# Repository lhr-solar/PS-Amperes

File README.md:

# BPS-AmperesPCB - Firmware

- To do: update readme

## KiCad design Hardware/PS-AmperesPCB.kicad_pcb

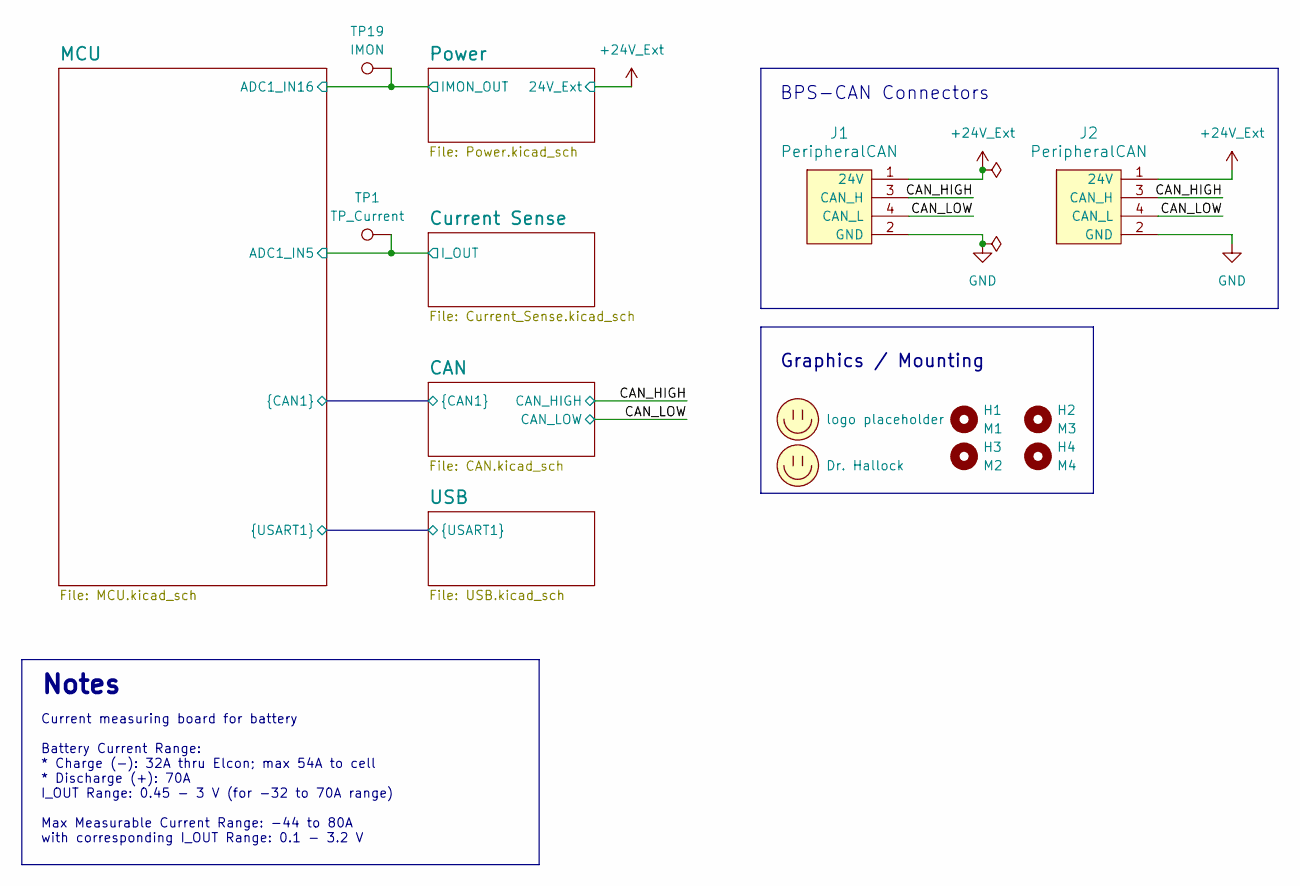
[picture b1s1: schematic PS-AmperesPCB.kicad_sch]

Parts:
H1: M1; MountingHole_3.2mm_M3_DIN965_Pad_TopBottom
H2: M3; MountingHole_3.2mm_M3_DIN965_Pad_TopBottom
H3: M2; MountingHole_3.2mm_M3_DIN965_Pad_TopBottom
H4: M4; MountingHole_3.2mm_M3_DIN965_Pad_TopBottom
J1, J2: PeripheralCAN; Molex_Nano-Fit_105309-xx04_1x04_P2.50mm_Vertical
LOGO1: logo placeholder; LHRs_LOGO
LOGO2: Dr. Hallock; Hallock_Image_Tiny
TP1: TP_Current; TestPoint_Keystone_5005-5009_Compact
TP19: IMON; TestPoint_Keystone_5005-5009_Compact

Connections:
+24V_Ext: J1.1 (24V), J2.1 (24V); also elsewhere on the board
/CAN_HIGH: J1.3 (CAN_H), J2.3 (CAN_H); also elsewhere on the board
/CAN_LOW: J1.4 (CAN_L), J2.4 (CAN_L); also elsewhere on the board
/Current Sense/I_OUT: TP1.1; also elsewhere on the board
/MCU/ADC1_IN16: TP19.1; also elsewhere on the board
GND: J1.2 (GND), J2.2 (GND); also elsewhere on the board

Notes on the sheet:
Notes
Graphics / Mounting
Current measuring board for battery Battery Current Range: * Charge (-): 32A thru Elcon; max 54A to cell * Discharge (+): 70A I_OUT Range: 0.45 - 3 V (for -32 to 70A range) Max Measurable Current Range: -44 to 80A with corresponding I_OUT Range: 0.1 - 3.2 V
BPS-CAN Connectors

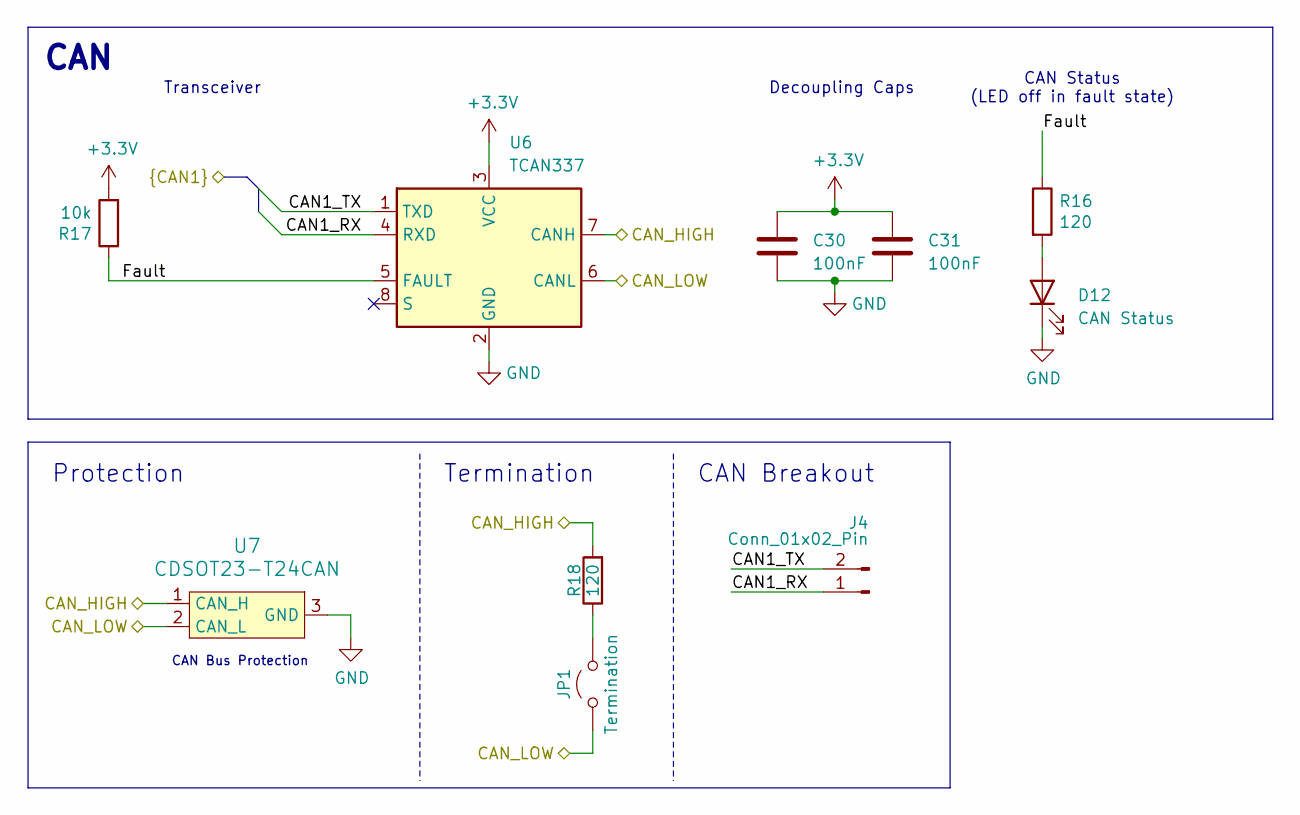
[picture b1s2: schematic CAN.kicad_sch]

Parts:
C30, C31: 100nF; C_0603_1608Metric_Pad1.08x0.95mm_HandSolder; Mouser Part Number 80-C0805C104M5R
D12: CAN Status; LED_0603_1608Metric_Pad1.05x0.95mm_HandSolder
J4: Conn_01x02_Pin; PinHeader_1x02_P2.54mm_Vertical
JP1: Termination; PinHeader_1x02_P2.54mm_Vertical
R16: 120; R_0603_1608Metric_Pad0.98x0.95mm_HandSolder; Mouser Part Number Inventory
R17: 10k; R_0603_1608Metric_Pad0.98x0.95mm_HandSolder
R18: 120; R_0603_1608Metric_Pad0.98x0.95mm_HandSolder; Mouser Part Number 71-CRCW080559R0FKEA
U6: TCAN337; TCAN337DCNR
U7: CDSOT23-T24CAN

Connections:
+3.3V: C30.1, C31.1, R17.2, U6.3 (VCC); also elsewhere on the board
/CAN/CAN1_RX: J4.1, U6.4 (RXD); also elsewhere on the board
/CAN/CAN1_TX: J4.2, U6.1 (TXD); also elsewhere on the board
/CAN/Fault: R16.1, R17.1, U6.5 (FAULT)
/CAN_HIGH: R18.2, U6.7 (CANH), U7.1 (CAN_H); also elsewhere on the board
/CAN_LOW: JP1.1 (A), U6.6 (CANL), U7.2 (CAN_L); also elsewhere on the board
GND: C30.2, C31.2, D12.1 (K), U6.2 (GND), U7.3 (GND); also elsewhere on the board
unnamed: D12.2 (A), R16.2
unnamed: JP1.2 (B), R18.1

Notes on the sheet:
Transceiver
CAN Breakout
Decoupling Caps
Protection
CAN Status (LED off in fault state)
Termination
CAN
CAN Bus Protection

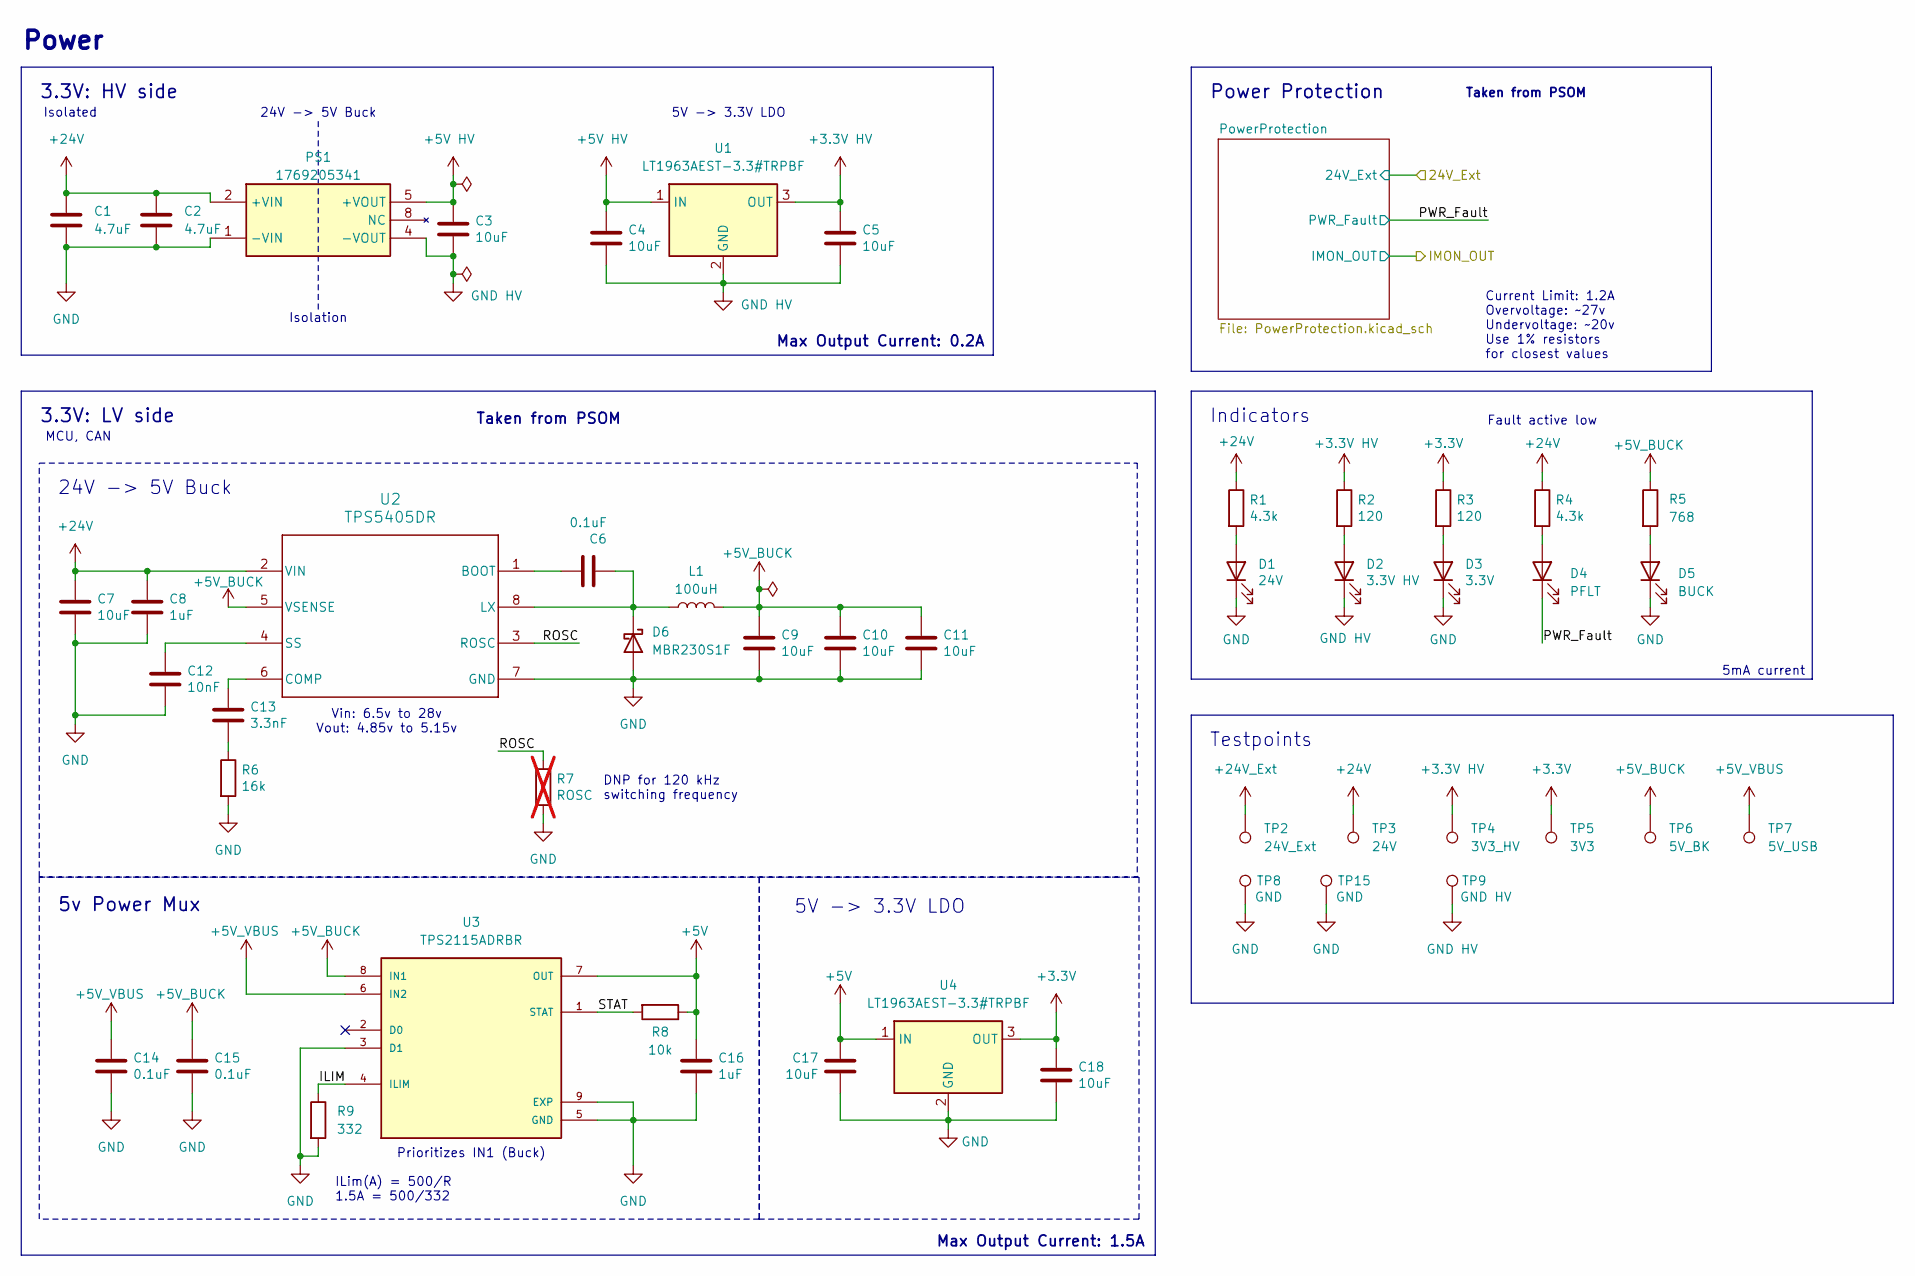
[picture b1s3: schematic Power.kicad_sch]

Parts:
C1, C2: 4.7uF; C_0805_2012Metric_Pad1.18x1.45mm_HandSolder
C3, C4, C5, C7, C9, C10, C11, C17, C18: 10uF; C_0805_2012Metric_Pad1.18x1.45mm_HandSolder
C6, C14, C15: 0.1uF; C_0603_1608Metric_Pad1.08x0.95mm_HandSolder
C8, C16: 1uF; C_0603_1608Metric_Pad1.08x0.95mm_HandSolder
C12: 10nF; C_0603_1608Metric_Pad1.08x0.95mm_HandSolder
C13: 3.3nF; C_0603_1608Metric_Pad1.08x0.95mm_HandSolder
D1: 24V; LED_0603_1608Metric_Pad1.05x0.95mm_HandSolder
D2: 3.3V HV; LED_0603_1608Metric_Pad1.05x0.95mm_HandSolder
D3: 3.3V; LED_0603_1608Metric_Pad1.05x0.95mm_HandSolder
D4: PFLT; LED_0603_1608Metric_Pad1.05x0.95mm_HandSolder
D5: BUCK; LED_0603_1608Metric_Pad1.05x0.95mm_HandSolder
D6: MBR230S1F; D_SOD-123F
L1: 100uH; L_Coilcraft_MSS1246-XXX
PS1: 1769205341; WE_1769205341; Mouser Part Number 710-1769205341
R1, R4: 4.3k; R_0603_1608Metric_Pad0.98x0.95mm_HandSolder
R2, R3: 120; R_0603_1608Metric_Pad0.98x0.95mm_HandSolder
R5: 768; R_0603_1608Metric_Pad0.98x0.95mm_HandSolder
R6: 16k; R_0603_1608Metric_Pad0.98x0.95mm_HandSolder
R7: ROSC; R_0603_1608Metric_Pad0.98x0.95mm_HandSolder; not fitted
R8: 10k; R_0603_1608Metric_Pad0.98x0.95mm_HandSolder
R9: 332; R_0603_1608Metric_Pad0.98x0.95mm_HandSolder
TP2: 24V_Ext; TestPoint_Pad_1.0x1.0mm
TP3: 24V; TestPoint_Pad_1.0x1.0mm
TP4: 3V3_HV; TestPoint_Pad_1.0x1.0mm
TP5: 3V3; TestPoint_Pad_1.0x1.0mm
TP6: 5V_BK; TestPoint_Pad_1.0x1.0mm
TP7: 5V_USB; TestPoint_Pad_1.0x1.0mm
TP8, TP15: GND; TestPoint_Pad_1.0x1.0mm
TP9: GND HV; TestPoint_Pad_1.0x1.0mm
U1, U4: LT1963AEST-3.3#TRPBF; SOT-223-3_TabPin2
U2: TPS5405DR
U3: TPS2115ADRBR; VSON-8-1EP_3x3mm_P0.65mm_EP1.65x2.4mm

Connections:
+3.3V: C18.1, R3.1, TP5.1, U4.3 (OUT); also elsewhere on the board
+3.3V HV: C5.1, R2.1, TP4.1, U1.3 (OUT); also elsewhere on the board
+5V: C16.1, C17.1, R8.1, U3.7 (OUT), U4.1 (IN)
+5V HV: C3.1, C4.1, PS1.5 (+VOUT), U1.1 (IN)
+5V_BUCK: C9.1, C10.1, C11.1, C15.1, L1.2, R5.1, TP6.1, U2.5 (VSENSE), U3.8 (IN1)
+5V_VBUS: C14.1, TP7.1, U3.6 (IN2); also elsewhere on the board
+24V: C1.1, C2.1, C7.1, C8.1, PS1.2 (+VIN), R1.1, R4.1, TP3.1, U2.2 (VIN); also elsewhere on the board
+24V_Ext: TP2.1; also elsewhere on the board
/Power/ILIM: R9.1, U3.4 (ILIM)
/Power/PWR_Fault: D4.1 (K); also elsewhere on the board
/Power/ROSC: R7.1, U2.3 (ROSC)
/Power/STAT: R8.2, U3.1 (STAT)
GND: C1.2, C2.2, C7.2, C8.2, C9.2, C10.2, C11.2, C12.2, C14.2, C15.2, C16.2, C17.2, C18.2, D1.1 (K), D3.1 (K), D5.1 (K), D6.2 (A), PS1.1 (-VIN), R6.2, R7.2, R9.2, TP8.1, TP15.1, U2.7 (GND), U3.3 (D1), U3.5 (GND), U3.9 (EXP), U4.2 (GND); also elsewhere on the board
GND HV: C3.2, C4.2, C5.2, D2.1 (K), PS1.4 (-VOUT), TP9.1, U1.2 (GND); also elsewhere on the board
unnamed: C13.2, R6.1
unnamed: D1.2 (A), R1.2
unnamed: D2.2 (A), R2.2
unnamed: D3.2 (A), R3.2
unnamed: D4.2 (A), R4.2
unnamed: D5.2 (A), R5.2
unnamed: C6.2, D6.1 (K), L1.1, U2.8 (LX)
unnamed: C6.1, U2.1 (BOOT)
unnamed: C13.1, U2.6 (COMP)
unnamed: C12.1, U2.4 (SS)

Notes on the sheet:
Isolation
Max Output Current: 1.5A
Power
Testpoints
Isolated
Taken from PSOM
Indicators
Max Output Current: 0.2A
3.3V: HV side
Prioritizes IN1 (Buck)
5v Power Mux
24V -> 5V Buck
5V -> 3.3V LDO
Current Limit: 1.2A Overvoltage: ~27v Undervoltage: ~20v Use 1% resistors for closest values
DNP for 120 kHz switching frequency
ILim(A) = 500/R 1.5A = 500/332
Vin: 6.5v to 28v Vout: 4.85v to 5.15v
5mA current
MCU, CAN
3.3V: LV side
Power Protection
Fault active low

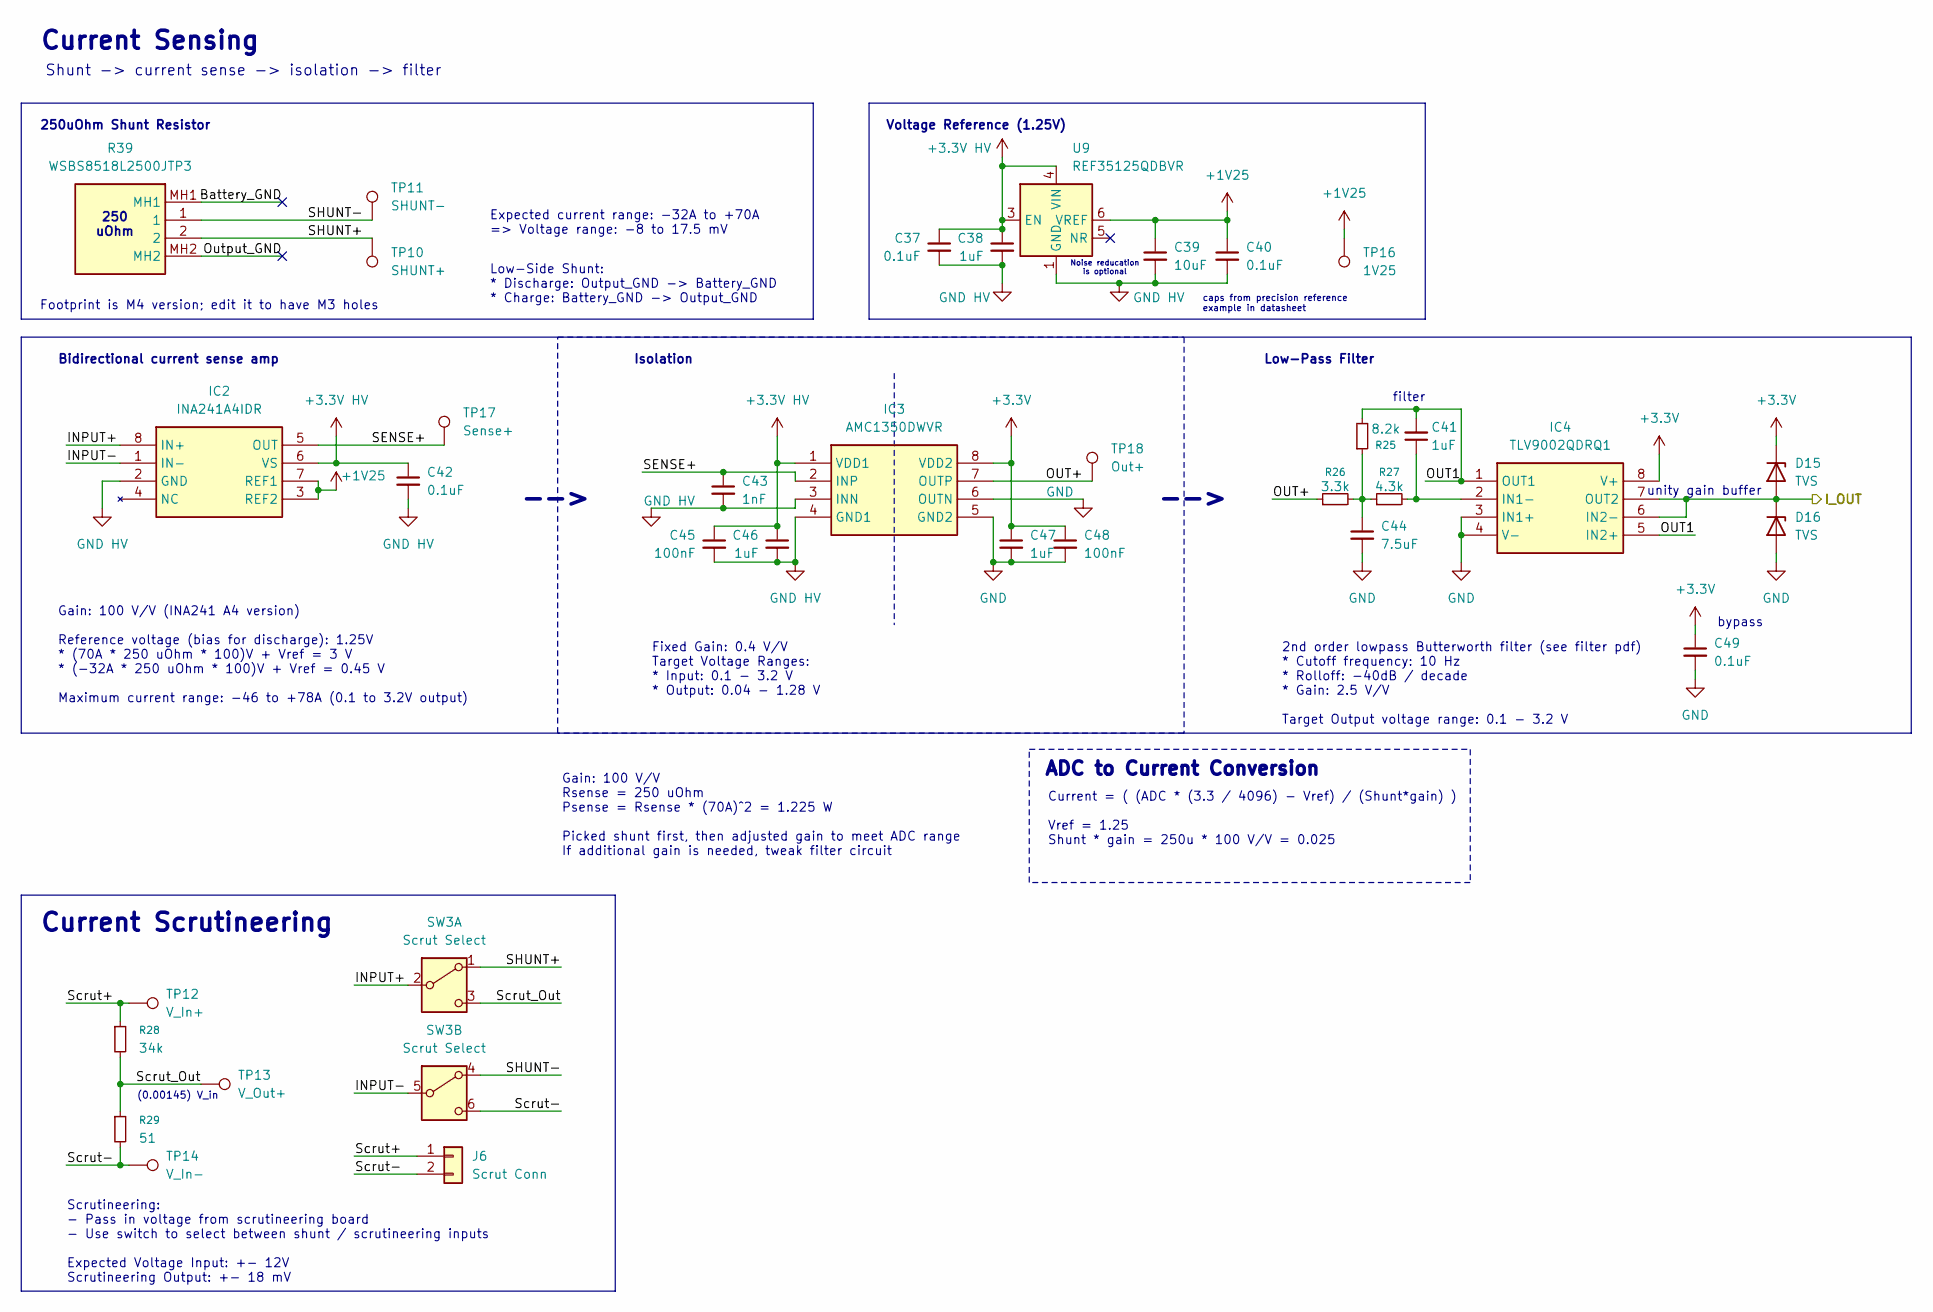
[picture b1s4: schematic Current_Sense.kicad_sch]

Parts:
C37, C40, C42, C49: 0.1uF; C_0603_1608Metric_Pad1.08x0.95mm_HandSolder
C38, C41, C46, C47: 1uF; C_0603_1608Metric_Pad1.08x0.95mm_HandSolder
C39: 10uF; C_0805_2012Metric_Pad1.18x1.45mm_HandSolder
C43: 1nF; C_0603_1608Metric_Pad1.08x0.95mm_HandSolder
C44: 7.5uF; C_0603_1608Metric_Pad1.08x0.95mm_HandSolder
C45, C48: 100nF; C_0603_1608Metric_Pad1.08x0.95mm_HandSolder
D15, D16: TVS; D_SOD-123F; Mouser Part Number 576-SMF3.3
IC2: INA241A4IDR; INA241A5IDR; Mouser Part Number 595-INA241A4IDR
IC3: AMC1350DWVR; Mouser Part Number 595-AMC1350DWVR
IC4: TLV9002QDRQ1; Mouser Part Number 595-TLV9002QDRQ1
J6: Scrut Conn; Molex_Nano-Fit_105309-xx02_1x02_P2.50mm_Vertical
R25: 8.2k; R_0603_1608Metric_Pad0.98x0.95mm_HandSolder
R26: 3.3k; R_0603_1608Metric_Pad0.98x0.95mm_HandSolder
R27: 4.3k; R_0603_1608Metric_Pad0.98x0.95mm_HandSolder
R28: 34k; R_0603_1608Metric_Pad0.98x0.95mm_HandSolder
R29: 51; R_0603_1608Metric_Pad0.98x0.95mm_HandSolder
R39: WSBS8518L2500JTP3; WSBS8518L2500JKM4; Mouser Part Number 71-WSBS8518L2500JTP3
SW3: Scrut Select; CAS220TB
TP10: SHUNT+; TestPoint_Pad_1.0x1.0mm
TP11: SHUNT-; TestPoint_Pad_1.0x1.0mm
TP12: V_In+; TestPoint_Pad_1.0x1.0mm
TP13: V_Out+; TestPoint_Pad_1.0x1.0mm
TP14: V_In-; TestPoint_Pad_1.0x1.0mm
TP16: 1V25; TestPoint_Pad_1.0x1.0mm
TP17: Sense+; TestPoint_Keystone_5005-5009_Compact
TP18: Out+; TestPoint_Keystone_5005-5009_Compact
U9: REF35125QDBVR; SOT-23-6

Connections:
+1V25: C39.1, C40.1, IC2.3 (REF2), IC2.7 (REF1), TP16.1, U9.6 (VREF)
+3.3V: C47.1, C48.1, C49.1, D15.1 (K), IC3.8 (VDD2), IC4.8 (V+); also elsewhere on the board
+3.3V HV: C37.1, C38.1, C42.1, C45.1, C46.1, IC2.6 (VS), IC3.1 (VDD1), U9.3 (EN), U9.4 (VIN); also elsewhere on the board
/Current Sense/Battery_GND: R39.MH1
/Current Sense/INPUT+: IC2.8 (IN+), SW3.2 (B)
/Current Sense/INPUT-: IC2.1 (IN-), SW3.5 (B)
/Current Sense/I_OUT: D15.2 (A), D16.1 (K), IC4.6 (IN2-), IC4.7 (OUT2); also elsewhere on the board
/Current Sense/OUT1: C41.2, IC4.1 (OUT1), IC4.5 (IN2+), R25.2
/Current Sense/OUT+: IC3.7 (OUTP), R26.1, TP18.1
/Current Sense/Output_GND: R39.MH2
/Current Sense/SENSE+: C43.1, IC2.5 (OUT), IC3.2 (INP), TP17.1
/Current Sense/SHUNT+: R39.2, SW3.1 (A), TP10.1
/Current Sense/SHUNT-: R39.1, SW3.4 (A), TP11.1
/Current Sense/Scrut+: J6.1, R28.1, TP12.1
/Current Sense/Scrut-: J6.2, R29.2, SW3.6 (C), TP14.1
/Current Sense/Scrut_Out: R28.2, R29.1, SW3.3 (C), TP13.1
GND: C44.2, C47.2, C48.2, C49.2, D16.2 (A), IC3.5 (GND2), IC3.6 (OUTN), IC4.3 (IN1+), IC4.4 (V-); also elsewhere on the board
GND HV: C37.2, C38.2, C39.2, C40.2, C42.2, C43.2, C45.2, C46.2, IC2.2 (GND), IC3.3 (INN), IC3.4 (GND1), U9.1 (GND), U9.2 (GND); also elsewhere on the board
unnamed: C44.1, R25.1, R26.2, R27.1
unnamed: C41.1, IC4.2 (IN1-), R27.2

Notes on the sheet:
Gain: 100 V/V (INA241 A4 version) Reference voltage (bias for discharge): 1.25V * (70A * 250 uOhm * 100)V + Vref = 3 V * (-32A * 250 uOhm * 100)V + Vref = 0.45 V Maximum current range: -46 to +78A (0.1 to 3.2V output)
-->
(0.00145) V_in
filter
unity gain buffer
Current Sensing
Fixed Gain: 0.4 V/V Target Voltage Ranges: * Input: 0.1 - 3.2 V * Output: 0.04 - 1.28 V
Bidirectional current sense amp
Current = ( (ADC * (3.3 / 4096) - Vref) / (Shunt*gain) ) Vref = 1.25 Shunt * gain = 250u * 100 V/V = 0.025
Gain: 100 V/V Rsense = 250 uOhm Psense = Rsense * (70A)^2 = 1.225 W Picked shunt first, then adjusted gain to meet ADC range If additional gain is needed, tweak filter circuit
Low-Side Shunt: * Discharge: Output_GND -> Battery_GND * Charge: Battery_GND -> Output_GND
ADC to Current Conversion
Isolation
Low-Pass Filter
250 uOhm
Scrutineering: - Pass in voltage from scrutineering board - Use switch to select between shunt / scrutineering inputs Expected Voltage Input: +- 12V Scrutineering Output: +- 18 mV
Shunt -> current sense -> isolation -> filter
Current Scrutineering
Voltage Reference (1.25V)
250uOhm Shunt Resistor
bypass
caps from precision reference example in datasheet
Expected current range: -32A to +70A => Voltage range: -8 to 17.5 mV
2nd order lowpass Butterworth filter (see filter pdf) * Cutoff frequency: 10 Hz * Rolloff: -40dB / decade * Gain: 2.5 V/V Target Output voltage range: 0.1 - 3.2 V
Noise reducation is optional
Footprint is M4 version; edit it to have M3 holes

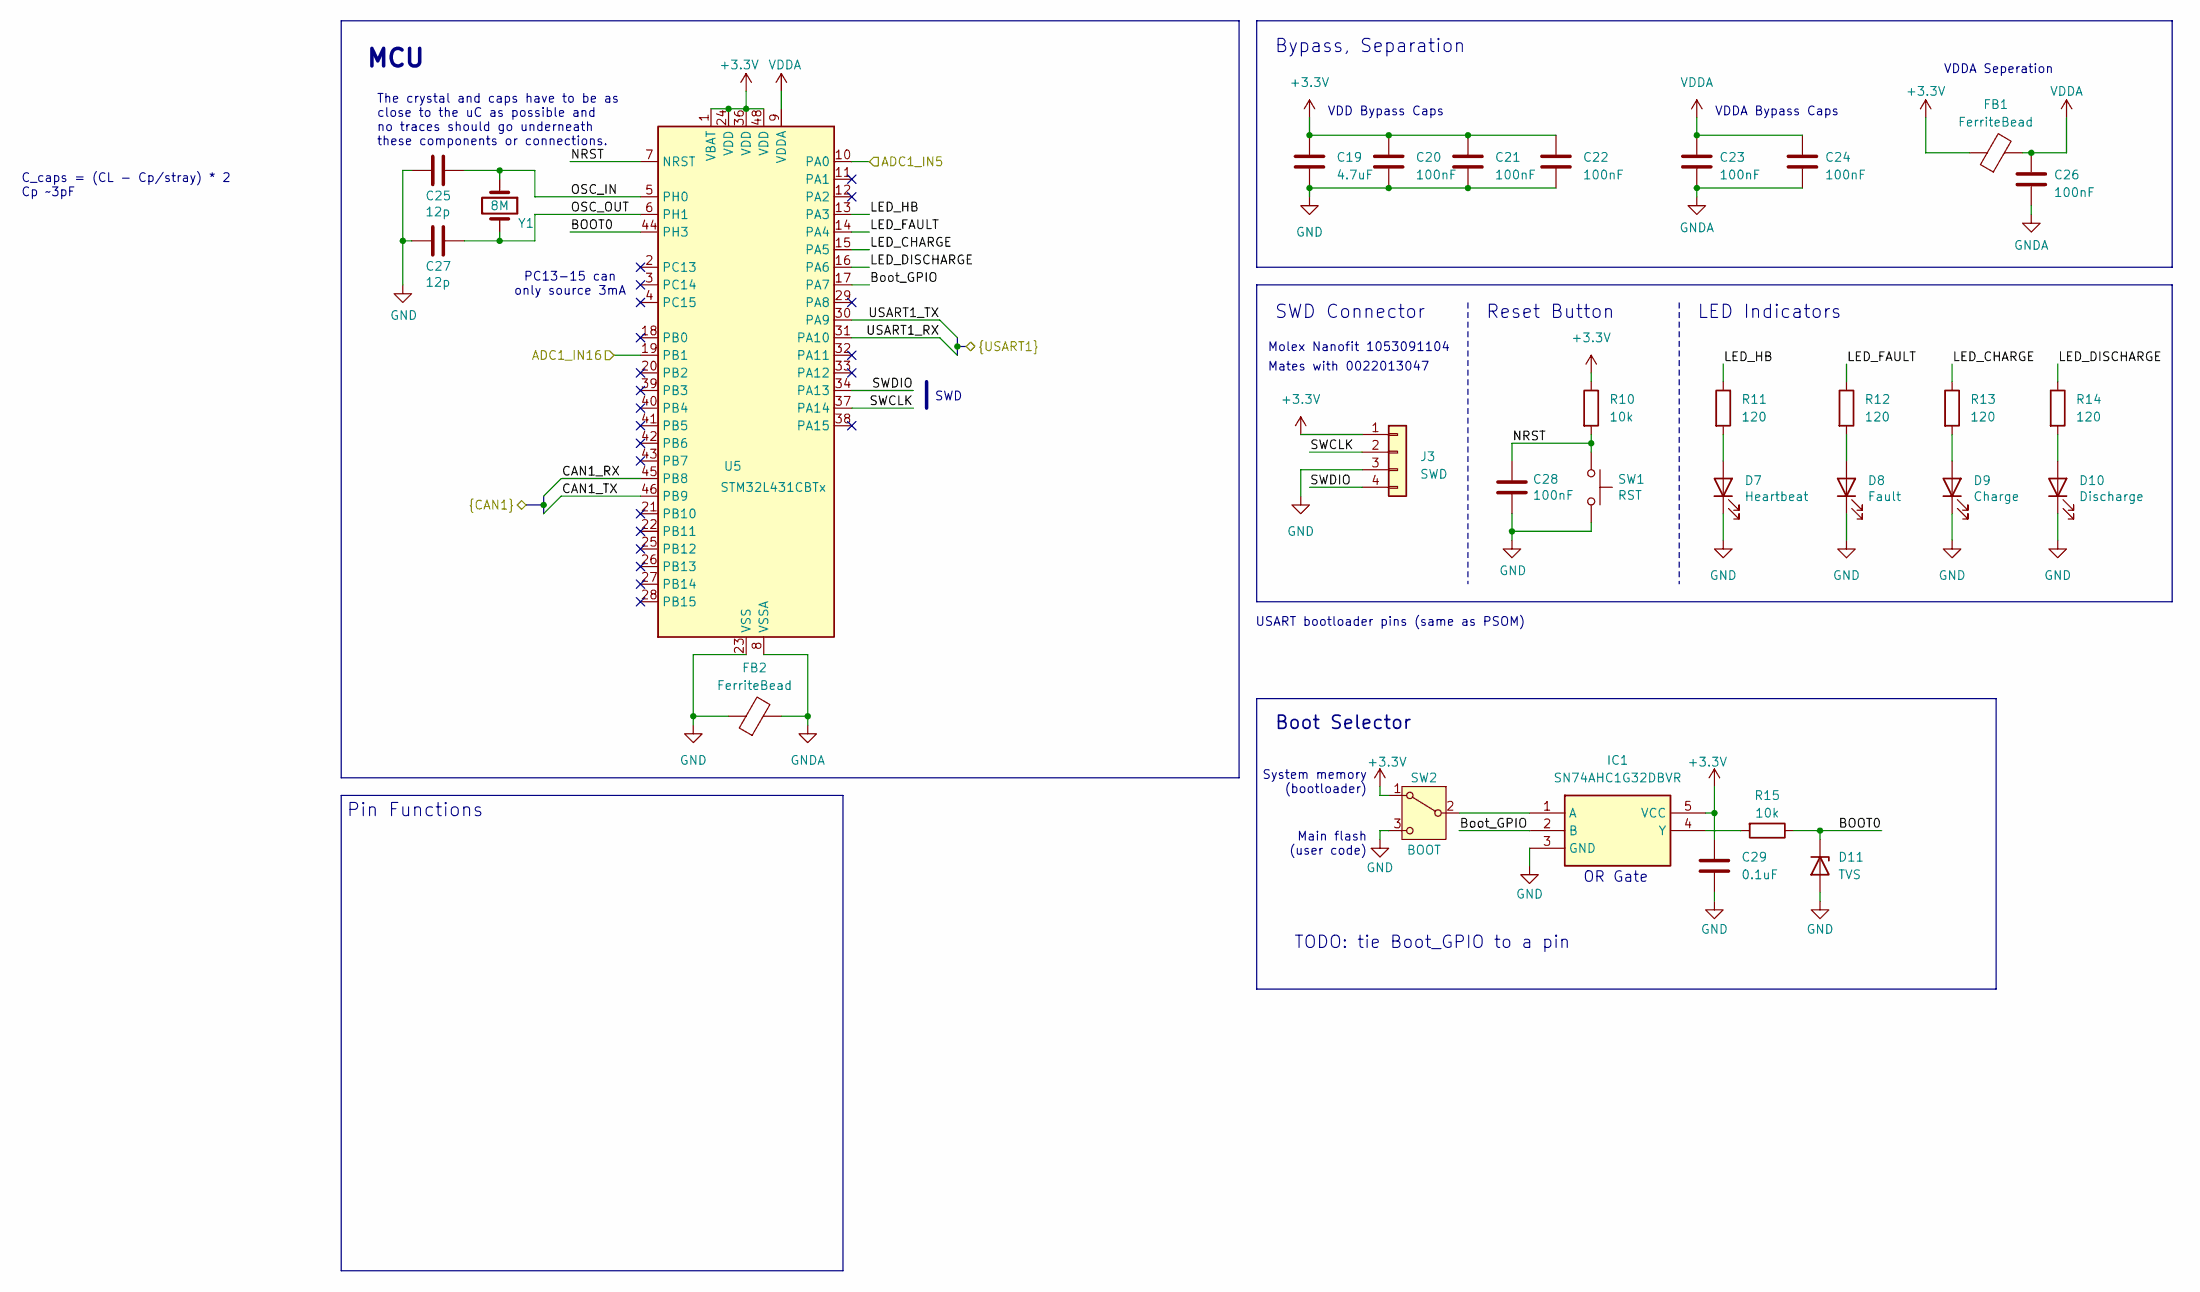
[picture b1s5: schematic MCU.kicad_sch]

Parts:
C19: 4.7uF; C_0805_2012Metric_Pad1.18x1.45mm_HandSolder
C20, C21, C22, C23, C24, C26, C28: 100nF; C_0603_1608Metric_Pad1.08x0.95mm_HandSolder; Mouser Part Number 80-C0805C104M5R
C25, C27: 12p; C_0603_1608Metric_Pad1.08x0.95mm_HandSolder; Mouser Part Number 80-C0805C120K5HACTU
C29: 0.1uF; C_0603_1608Metric_Pad1.08x0.95mm_HandSolder; Mouser Part Number 80-C0805C104M5R
D7: Heartbeat; LED_0603_1608Metric_Pad1.05x0.95mm_HandSolder
D8: Fault; LED_0603_1608Metric_Pad1.05x0.95mm_HandSolder
D9: Charge; LED_0603_1608Metric_Pad1.05x0.95mm_HandSolder
D10: Discharge; LED_0603_1608Metric_Pad1.05x0.95mm_HandSolder
D11: TVS; D_SOD-123F
FB1, FB2: FerriteBead; C_0603_1608Metric_Pad1.08x0.95mm_HandSolder; Mouser Part Number 704-MFBW1V2012-121-R
IC1: SN74AHC1G32DBVR; Mouser Part Number 595-SN74AHC1G32DBVR
J3: SWD; Molex_Nano-Fit_105309-xx04_1x04_P2.50mm_Vertical
R10: 10k; R_0603_1608Metric_Pad0.98x0.95mm_HandSolder; Mouser Part Number 71-CRCW080510K0FKEAC
R11, R12, R13, R14: 120; R_0603_1608Metric_Pad0.98x0.95mm_HandSolder
R15: 10k; R_0603_1608Metric_Pad0.98x0.95mm_HandSolder
SW1: RST; SW_TL3365AF180QG
SW2: BOOT; SW_CJS-1200TA
U5: STM32L431CBTx; LQFP-48_7x7mm_P0.5mm; Mouser Part Number 511-STM32L431CBT6
Y1: 8M; Crystal_SMD_Abracon_ABM3-2Pin_5.0x3.2mm; Mouser Part Number 815-ABM3-8-D2Y-T

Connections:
+3.3V: C19.1, C20.1, C21.1, C22.1, C29.1, FB1.1, IC1.5 (VCC), J3.1, R10.1, SW2.1 (A), U5.1 (VBAT), U5.24 (VDD), U5.36 (VDD), U5.48 (VDD); also elsewhere on the board
/CAN/CAN1_RX: U5.45 (PB8); also elsewhere on the board
/CAN/CAN1_TX: U5.46 (PB9); also elsewhere on the board
/Current Sense/I_OUT: U5.10 (PA0); also elsewhere on the board
/MCU/ADC1_IN16: U5.19 (PB1); also elsewhere on the board
/MCU/BOOT0: D11.1 (K), R15.1, U5.44 (PH3)
/MCU/Boot_GPIO: IC1.2 (B), U5.17 (PA7)
/MCU/LED_CHARGE: R13.1, U5.15 (PA5)
/MCU/LED_DISCHARGE: R14.1, U5.16 (PA6)
/MCU/LED_FAULT: R12.1, U5.14 (PA4)
/MCU/LED_HB: R11.1, U5.13 (PA3)
/MCU/NRST: C28.1, R10.2, SW1.1, U5.7 (NRST)
/MCU/OSC_IN: C25.1, U5.5 (PH0), Y1.1
/MCU/OSC_OUT: C27.1, U5.6 (PH1), Y1.2
/MCU/SWCLK: J3.2, U5.37 (PA14)
/MCU/SWDIO: J3.4, U5.34 (PA13)
/MCU/USART1_RX: U5.31 (PA10); also elsewhere on the board
/MCU/USART1_TX: U5.30 (PA9); also elsewhere on the board
GND: C19.2, C20.2, C21.2, C22.2, C25.2, C27.2, C28.2, C29.2, D7.1 (K), D8.1 (K), D9.1 (K), D10.1 (K), D11.2 (A), FB2.1, IC1.3 (GND), J3.3, SW1.2, SW2.3 (C), U5.23 (VSS), U5.35 (VSS), U5.47 (VSS); also elsewhere on the board
GNDA: C23.2, C24.2, C26.2, FB2.2, U5.8 (VSSA)
unnamed: D7.2 (A), R11.2
unnamed: D8.2 (A), R12.2
unnamed: D9.2 (A), R13.2
unnamed: D10.2 (A), R14.2
unnamed: IC1.1 (A), SW2.2 (B)
unnamed: IC1.4 (Y), R15.2
VDDA: C23.1, C24.1, C26.1, FB1.2, U5.9 (VDDA)

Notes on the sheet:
SWD
Pin Functions
LED Indicators
Molex Nanofit 1053091104
PC13-15 can only source 3mA
MCU
Mates with 0022013047
The crystal and caps have to be as close to the uC as possible and no traces should go underneath these components or connections.
SWD Connector
C_caps = (CL - Cp/stray) * 2 Cp ~3pF
System memory (bootloader)
Reset Button
Boot Selector
USART bootloader pins (same as PSOM)
VDDA Bypass Caps
TODO: tie Boot_GPIO to a pin
VDD Bypass Caps
VDDA Seperation
OR Gate
Bypass, Separation
Main flash (user code)

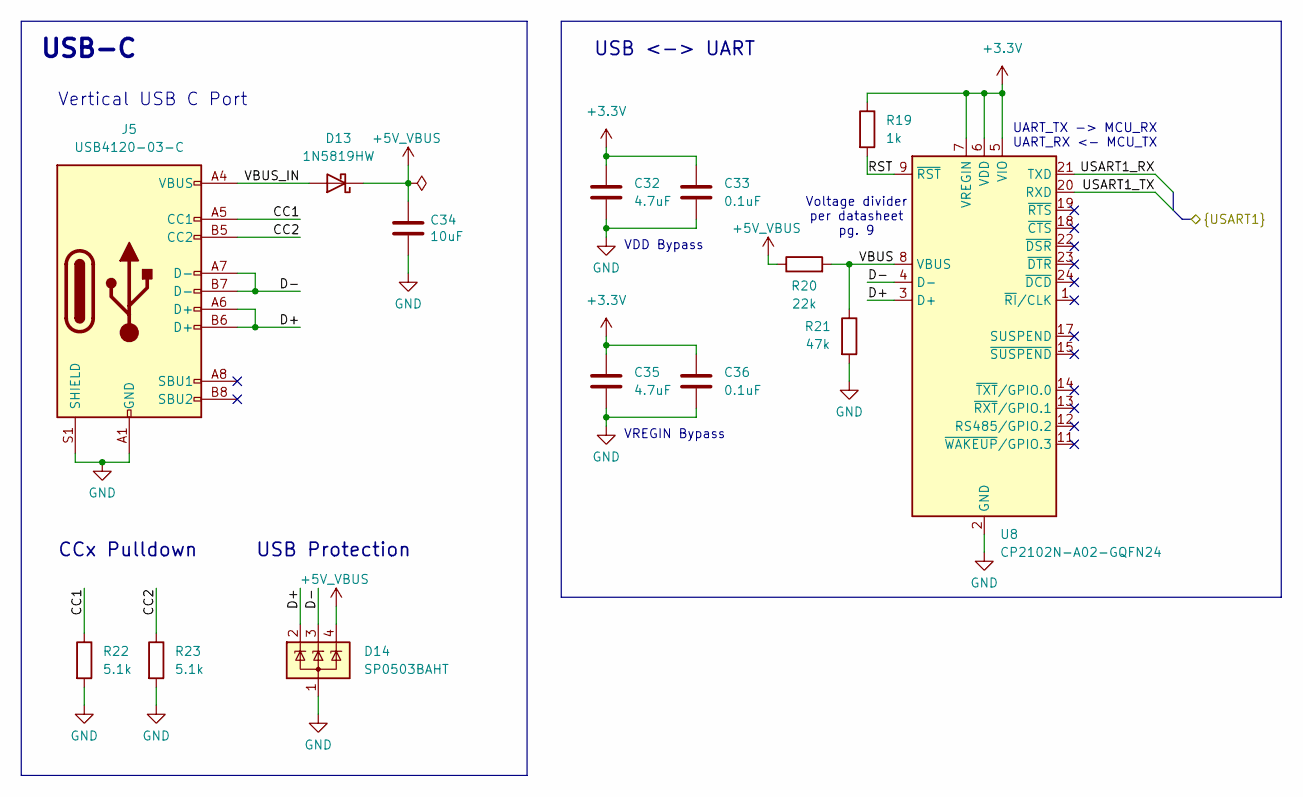
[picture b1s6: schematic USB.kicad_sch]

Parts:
C32, C35: 4.7uF; C_0805_2012Metric_Pad1.18x1.45mm_HandSolder
C33, C36: 0.1uF; C_0603_1608Metric_Pad1.08x0.95mm_HandSolder
C34: 10uF; C_0805_2012Metric_Pad1.18x1.45mm_HandSolder
D13: 1N5819HW; D_SOD-123
D14: SP0503BAHT; SOT-143; Mouser Part Number 576-SP0503BAHTG
J5: USB4120-03-C; USB412003C
R19: 1k; R_0603_1608Metric_Pad0.98x0.95mm_HandSolder
R20: 22k; R_0603_1608Metric_Pad0.98x0.95mm_HandSolder
R21: 47k; R_0603_1608Metric_Pad0.98x0.95mm_HandSolder
R22, R23: 5.1k; R_0603_1608Metric_Pad0.98x0.95mm_HandSolder
U8: CP2102N-A02-GQFN24

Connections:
+3.3V: C32.1, C33.1, C35.1, C36.1, R19.1, U8.5 (VIO), U8.6 (VDD), U8.7 (VREGIN); also elsewhere on the board
+5V_VBUS: C34.1, D13.1 (K), D14.4 (K), R20.1; also elsewhere on the board
/MCU/USART1_RX: U8.21 (TXD); also elsewhere on the board
/MCU/USART1_TX: U8.20 (RXD); also elsewhere on the board
/USB/CC1: J5.A5 (CC1), R22.1
/USB/CC2: J5.B5 (CC2), R23.1
/USB/D+: D14.2 (K), J5.A6 (D+), J5.B6 (D+), U8.3 (D+)
/USB/D-: D14.3 (K), J5.A7 (D-), J5.B7 (D-), U8.4 (D-)
/USB/RST: R19.2, U8.9 (~RST)
/USB/VBUS: R20.2, R21.1, U8.8 (VBUS)
/USB/VBUS_IN: D13.2 (A), J5.A4 (VBUS), J5.A9 (VBUS), J5.B4 (VBUS), J5.B9 (VBUS)
GND: C32.2, C33.2, C34.2, C35.2, C36.2, D14.1 (A), J5.A1 (GND), J5.A12 (GND), J5.B1 (GND), J5.B12 (GND), J5.S1 (SHIELD), R21.2, R22.2, R23.2, U8.2 (GND), U8.25 (GND); also elsewhere on the board

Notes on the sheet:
USB-C
USB <-> UART
Voltage divider per datasheet pg. 9
Vertical USB C Port
VDD Bypass
CCx Pulldown
UART_TX -> MCU_RX UART_RX <- MCU_TX
VREGIN Bypass
USB Protection

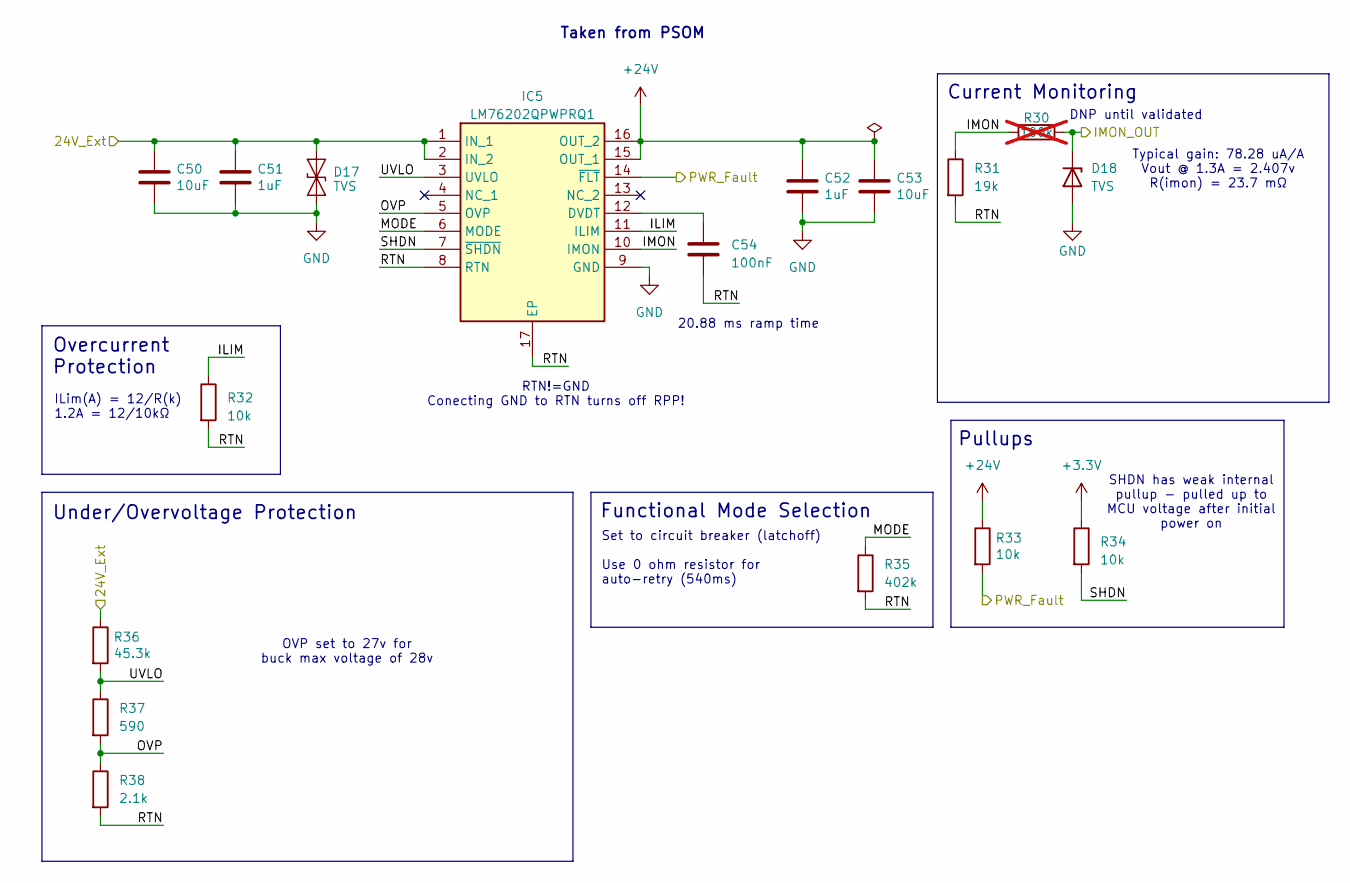
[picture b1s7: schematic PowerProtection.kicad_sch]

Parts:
C50, C53: 10uF; C_0805_2012Metric_Pad1.18x1.45mm_HandSolder
C51, C52: 1uF; C_0603_1608Metric_Pad1.08x0.95mm_HandSolder
C54: 100nF; C_0603_1608Metric_Pad1.08x0.95mm_HandSolder
D17: TVS; D_SOD-323_HandSoldering
D18: TVS; D_SOD-123F
IC5: LM76202QPWPRQ1; Mouser Part Number 595-LM76202QPWPRQ1
R30: 100k; R_0603_1608Metric_Pad0.98x0.95mm_HandSolder; not fitted
R31: 19k; R_0603_1608Metric_Pad0.98x0.95mm_HandSolder
R32, R33, R34: 10k; R_0603_1608Metric_Pad0.98x0.95mm_HandSolder
R35: 402k; R_0603_1608Metric_Pad0.98x0.95mm_HandSolder
R36: 45.3k; R_0603_1608Metric_Pad0.98x0.95mm_HandSolder
R37: 590; R_0603_1608Metric_Pad0.98x0.95mm_HandSolder
R38: 2.1k; R_0603_1608Metric_Pad0.98x0.95mm_HandSolder

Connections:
+3.3V: R34.1; also elsewhere on the board
+24V: C52.1, C53.1, IC5.15 (OUT_1), IC5.16 (OUT_2), R33.1; also elsewhere on the board
+24V_Ext: C50.1, C51.1, D17.2 (A2), IC5.1 (IN_1), IC5.2 (IN_2), R36.1; also elsewhere on the board
/MCU/ADC1_IN16: D18.1 (K), R30.2; also elsewhere on the board
/Power/PWR_Fault: IC5.14 (~FLT), R33.2; also elsewhere on the board
/Power/PowerProtection/ILIM: IC5.11 (ILIM), R32.1
/Power/PowerProtection/IMON: IC5.10 (IMON), R30.1, R31.1
/Power/PowerProtection/MODE: IC5.6 (MODE), R35.1
/Power/PowerProtection/OVP: IC5.5 (OVP), R37.2, R38.1
/Power/PowerProtection/RTN: C54.2, IC5.8 (RTN), IC5.17 (EP), R31.2, R32.2, R35.2, R38.2
/Power/PowerProtection/SHDN: IC5.7 (~SHDN), R34.2
/Power/PowerProtection/UVLO: IC5.3 (UVLO), R36.2, R37.1
GND: C50.2, C51.2, C52.2, C53.2, D17.1 (A1), D18.2 (A), IC5.9 (GND); also elsewhere on the board
unnamed: C54.1, IC5.12 (DVDT)

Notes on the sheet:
OVP set to 27v for buck max voltage of 28v
DNP until validated
RTN!=GND Conecting GND to RTN turns off RPP!
Under/Overvoltage Protection
Typical gain: 78.28 uA/A Vout @ 1.3A = 2.407v R(imon) = 23.7 mΩ
ILim(A) = 12/R(k) 1.2A = 12/10kΩ
SHDN has weak internal pullup - pulled up to MCU voltage after initial power on
20.88 ms ramp time
Set to circuit breaker (latchoff) Use 0 ohm resistor for auto-retry (540ms)
Pullups
Overcurrent Protection
Functional Mode Selection
Current Monitoring
Taken from PSOM
